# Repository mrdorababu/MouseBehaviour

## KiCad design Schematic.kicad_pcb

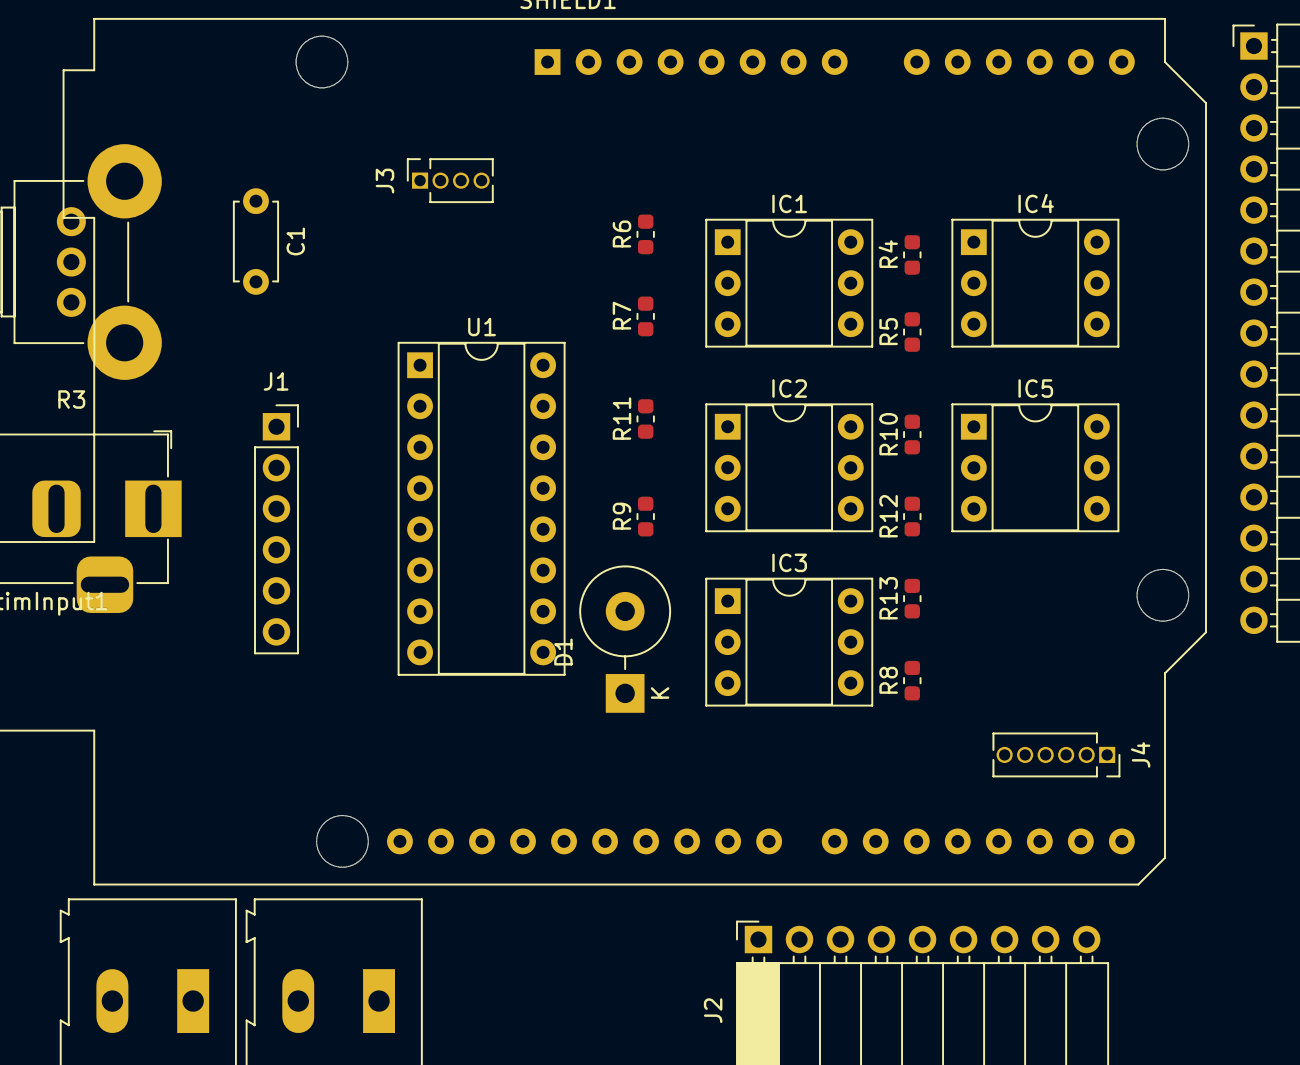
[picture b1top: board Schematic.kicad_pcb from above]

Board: 2 copper layers, 28 parts (0 on the bottom side), 34 nets, no tracks yet.

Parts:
C1: 47 uF; C_Disc_D4.7mm_W2.5mm_P5.00mm
CN1: OutputPad; PinHeader_1x15_P2.54mm_Horizontal
D1: DIODE; D_DO-27_P5.08mm_Vertical_KathodeUp
IC1, IC2, IC3, IC4, IC5: 4N35; DIP-6_W7.62mm_Socket
J1: SSR-ToInput; PinSocket_1x06_P2.54mm_Vertical
J2: SSR-ToOutput; PinSocket_1x09_P2.54mm_Horizontal
J3: RotaryEncoder; PinSocket_1x04_P1.27mm_Vertical
J4: AnalogIn; PinSocket_1x06_P1.27mm_Vertical
J-InStimInput1: 90V; BarrelJack_Horizontal
JPad1: ShockPad; TerminalBlock_Altech_AK300-2_P5.00mm
JPad2: StimInput; TerminalBlock_Altech_AK300-2_P5.00mm
R3: 1M; Potentiometer_Alps_RK09K_Single_Horizontal
R4, R10, R12: 560E; R_0603_1608Metric
R5, R6: 470E; R_0603_1608Metric
R7, R8, R9, R11, R13: 15k; R_0603_1608Metric
SHIELD1: ARDUINO_SHIELD; Arduino_UNO_R3_WithMountingHoles
U1: ULN2003A; DIP-16_W7.62mm_Socket

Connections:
5V: J1.1, J3.3
12 V: CN1.11, D1.1
A0: C1.1, J2.6, J4.1, R3.1
AGND: C1.2, CN1.1, CN1.10, CN1.12, CN1.14, J3.4, R3.2, R7.1, R8.2, R9.2, R11.2, R13.2, U1.8
D2: J3.1, SHIELD1.2
D3: J3.2, SHIELD1.3
D4: J1.3, J1.4, SHIELD1.4
D5: J2.8, SHIELD1.5
D6: J1.5, J1.6, SHIELD1.6
D7: JPad2.1, SHIELD1.7
D8: R12.1, SHIELD1.8
D9: R10.1, SHIELD1.9
D11: R5.1, SHIELD1.11
D12: R6.1, SHIELD1.12
D13: R4.1, SHIELD1.13
DGND: IC1.2, IC2.2, IC3.2, IC4.2, IC5.2, J1.2, JPad2.2
EX 5 V: CN1.9, IC1.5, IC2.5, IC3.5, IC4.5, IC5.5
unnamed: IC1.1, R4.2
unnamed: IC2.1, R5.2
unnamed: IC3.1, R6.2
unnamed: IC4.1, R10.2
unnamed: IC5.1, R12.2
unnamed: J2.1, J2.5, JPad1.2
unnamed: J2.3, J2.7, JPad1.1
unnamed: J2.2, J-InStimInput1.1
unnamed: J2.4, J-InStimInput1.2
Solenoid1_1: CN1.6, CN1.8, D1.2, U1.9
Solenoid1_2: CN1.7, U1.15
Solenoid2_2: CN1.5, U1.16
Tone1: CN1.15, IC4.4, R11.1
Tone2: CN1.13, IC5.4, R13.1
Tone3: CN1.2, IC1.4, R7.2
ULN_IN1: IC2.4, R9.1, U1.1
ULN_IN2: IC3.4, R8.1, U1.2

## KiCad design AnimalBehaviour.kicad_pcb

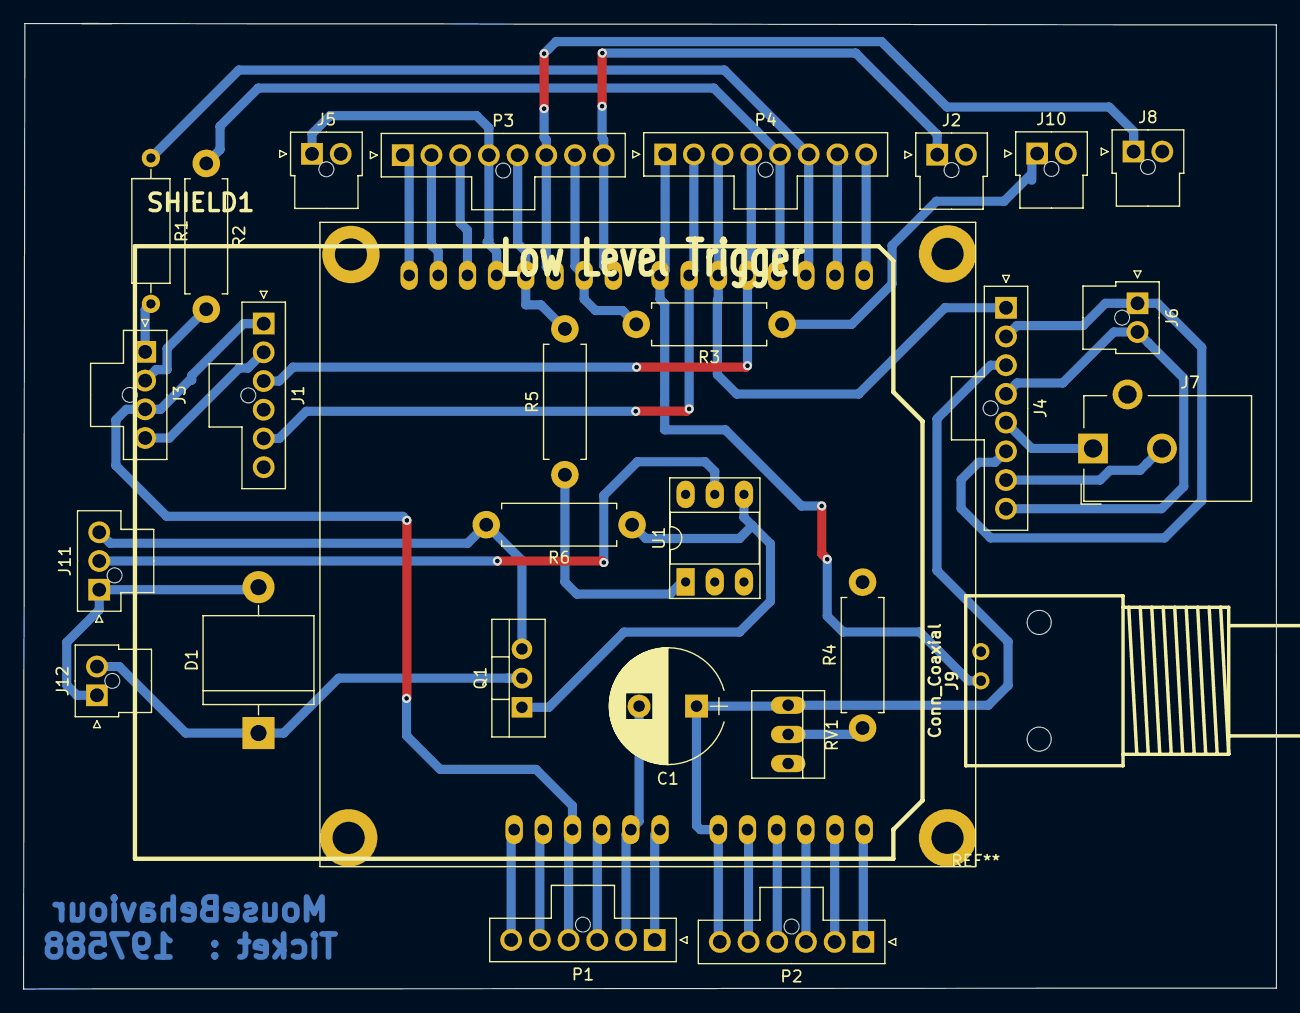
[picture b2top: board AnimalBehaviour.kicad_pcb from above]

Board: 2 copper layers, 109.1 x 84.1 mm, 28 parts (0 on the bottom side), 40 nets.

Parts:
C1: 47nF; CP_Radial_D10.0mm_P5.00mm
D1: DIODE; D_5KP_P12.70mm_Horizontal
J1: Conn_01x06_Male; Molex_NanoFit_1x06x2.50mm_Straight
J2, J5, J6, J8, J10, J12: Conn_01x02_Male; Molex_NanoFit_1x02x2.50mm_Straight
J3: Conn_01x04_Male; Molex_NanoFit_1x04x2.50mm_Straight
J4: Conn_01x08_Male; Molex_NanoFit_1x08x2.50mm_Straight
J7: Jack-DC; Barrel_Jack_CUI_PJ-102AH
J9: Conn_Coaxial; bnc_90_1-1337543-0
J11: Conn_01x03_Male; Molex_NanoFit_1x03x2.50mm_Straight
P1, P2: CONN_6; Molex_NanoFit_1x06x2.50mm_Straight
P3, P4: CONN_8; Molex_NanoFit_1x08x2.50mm_Straight
Q1: IRF540N; TO-220-3_Vertical
R1: 560E; R_Axial_DIN0309_L9.0mm_D3.2mm_P12.70mm_Horizontal
R2: 560E; R_Axial_DIN0411_L9.9mm_D3.6mm_P12.70mm_Horizontal
R3, R5: 470E; R_Axial_DIN0411_L9.9mm_D3.6mm_P12.70mm_Horizontal
R4: 1K; R_Axial_DIN0411_L9.9mm_D3.6mm_P12.70mm_Horizontal
R6: 10K; R_Axial_DIN0411_L9.9mm_D3.6mm_P12.70mm_Horizontal
RV1: 1 MegOhm; PINHEAD1-3
SHIELD1: ARDUINO_SHIELD; ARDUINO_SHIELD_040pins
U1: 4N35; DIP-6_W7.62mm_Socket_LongPads

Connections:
3V3: P1.5, SHIELD1.3V3
5V: J1.1, J3.3, P1.4, SHIELD1.5V
A0: C1.1, J4.3, P2.6, RV1.1, SHIELD1.AD0
A1: P2.5, SHIELD1.AD1
A2: P2.4, SHIELD1.AD2
A3: P2.3, SHIELD1.AD3
A4: P2.2, SHIELD1.AD4
A5: P2.1, SHIELD1.AD5
AGND: J11.3, Q1.3, R6.2
AREF: P3.1, SHIELD1.AREF
D0: P4.8, SHIELD1.0
D1: P4.7, SHIELD1.1
D2: P4.6, R1.1, SHIELD1.2
D3: P4.5, R2.1, SHIELD1.3
D4: J1.3, J1.4, P4.4, SHIELD1.4
D5: J4.1, P4.3, SHIELD1.5
D6: J1.5, J1.6, P4.2, SHIELD1.6
D7: J9.1, P4.1, SHIELD1.7
D8: J2.1, P3.8, SHIELD1.8
D9: P3.7, R3.2, SHIELD1.9
D10: J8.1, P3.6, SHIELD1.10
D11: P3.5, R5.2, SHIELD1.11
D12: J5.1, P3.4, SHIELD1.12
D13: P3.3, SHIELD1.13
DGND: C1.2, J1.2, J2.2, J3.4, J5.2, J8.2, J9.2, J10.2, P1.2, P1.3, P3.2, R4.2, SHIELD1.GND1, SHIELD1.GND2, SHIELD1.GND3, U1.2
EX_5V: J11.2, U1.5
EX_12V: D1.2, J11.1, J12.1
unnamed: D1.1, J12.2, Q1.2
unnamed: J3.1, R1.2
unnamed: J3.2, R2.2
unnamed: J10.1, R3.1
unnamed: Q1.1, R6.1, U1.4
unnamed: R4.1, RV1.2
unnamed: R5.1, U1.1
OUT+: J4.5, J7.1
OUT-: J4.7, J7.2
PAD+: J4.2, J4.6, J6.1
PAD-: J4.4, J4.8, J6.2
RST: P1.6, SHIELD1.RST
V_IN: P1.1, SHIELD1.V_IN

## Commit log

2019-04-04 Added shock pin to the arduino. #37
2019-07-05 Add files via upload
    PCB tracks updated
2019-07-05 moved to a folder.
